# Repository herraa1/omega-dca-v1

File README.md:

# Omega DC Adapter (DCA) v1

DC adapter for the [Omega Home Computer](https://github.com/skiselev/omega).

## Introduction

This is a simple DC adapter for the Omega Home Computer with the following features:

* External DC input power supply
* Wide input voltage from DC +6.5V to DC +24V
* Max input current of 4A
* Power control via external SPDT switch
* Output voltages:
    * 3x independent regulated DC +5V 1.5A (max 3A)
    * 1x independent regulated DC +12V 700mA and -12V 150mA
* Three independent power circuits
* Common Reverse Polarity Protection (RPP), protects the Omega Home Computer from connecting a power barrel with inverted polarity
* Per circuit thermal shutdown, protects the Omega DC Adapter from damage when operating at exceedingly high temperatures
* Per circuit shortcircuit and Over Current Protection (OCP), protects the Omega Home Computer from shorts or excessive current (typ 5.5A)
* Per circuit Over Voltage Protection (OVP), protects the Omega Home Computer from excessive high voltages (typ 5.52V)
* Per circuit Under Voltage Protection (UVP), protects the Omega Home Computer from excessive low voltages (typ ~3V)

## Rationale

When I upgraded my Omega Home Computer with an audio amplifier board and a floppy drive I detected that, no matter how good was the power supply used, the Omega Home Computer suffered sudden resets due to power-related issues when performing some operations like, for example:
* turning on the audio amplifier while the Omega Home Computer was turned on
* increasing the audio amplifier volume up beyond a certain limit when playing compute intensive games
* inserting a floppy disk

My Omega Home Computer was using the [dc-adapter 1.6b](https://msxmakers.design.blog/proyectos/omega-home-computer/mini-fuente-dc-dc/) from [msxmakers!](https://msxmakers.design.blog/) with an external 5V power supply.

I measured the peak power consumption of the Omega Home Computer at about 1.7A with the audio amplifier on and the floppy drive spinning.

I checked several +5V power supplies with no success:
* LJH074-050030W 5V 3A (the one I purchased with the Omega Home Computer kit)
* YU0508 5V 8A (another "white brand" PSU)
* KORAD KA3005P 30V 5A (my lab bench programmable power supply...)

I used an electronic load tester (DL24 150W) and a separate multimeter (VC99) to check the actual voltage of the power supplies under load (at the power supply connector end):
* LJH074-050030W 5V 3A -> dropped to 4.9V with a 2A load and 4.6V with a 3A load
* YU0508 5V 8A -> kept a steady 5.0V with a 3A load, although it went down to 4.7V when pushing it to 6A
* KORAD KA3005P 30V 5A -> dropped to 4.8V at 5V constant voltage with a 2A load, and to 4.7V with a 3A load (required adjusting voltage to 5.3V to get 5.0V at 3A load)

So according to those load tests and the observed peak power consumption, at least the 5V 8A power supply should be capable of powering the Omega Home Computer and its upgrades without issues.
But it was not the case.

So I assumed the specific power demands of the audio amplifier and the floppy drive were causing the problems (undervoltage?) on the power rail of the Omega Home Computer.
I decided to test if the problem went away by using a separate power supply for the audio amplifier/floppy and the Omega Home Computer. I connected two 5V power supplies with a common ground, one power supply to the Omega and the other to the audio amplifier board and floppy. And voilà, no more resets.

So in the end, I decided to design a small power adapter board to provide separate power circuits to the Omega Home Computer, the audio amplifier and video converter, and the floppy drive, and while at it, added several protections just in case something went wrong with the components.

As there are lots of cheap ready to use mini boards providing part of the requirements needed, I just built a "franken-board" cannibalizing other boards to achieve the final goal.
The Omega DC Adapter was born.

## Overview

The Omega DC Adapter is a small power adapter board to provide protected and regulated power to the Omega Home Computer.
It supports the connection of an external DC power supply and a power switch to control power to the computer.

The Omega DC Adapter provides 3 independent power circuits:
* circuit #1 provides power to the Omega Home Computer motherboard and FMPAC (+5V, +12V and -12V) using conectors J10 and J12
* circuit #2 provides power to the external floppy drive (+5V) using connector J8
* circuit #3 provides power to the audio amplifier (+5V) using connector J6 and to the video converter (+5V) using connector J7

## Board

The Omega DC Adapter PCB is a 2-layer design that glues a bunch of ready-to-use mini boards:
* An ideal diode board at U1 to provide Reverse Polarity Protection, i.e. to avoid damage to the Omega Home Computer if a power supply with an incorrect polarity is connected
* Three step down mini boards with thermal shutdown and over current protection at J9, J5 and J3 to provide +5V to the three separate power circuits
* Three over voltage protection mini boards at U2, U3 and U4 to protect the three separate power circuits from overvoltages
* One step up board at J11 to provide +12V and -12V from the 5V output of J9 to feed pins 48 and 50 of the cartridge slots and the FMPAC extension

There are aswell:
* two Positive Temperature Coeficient (PTC) resettable fuses to limit the amount of current delivered to the cartridge slots, as indicated by the [MSX Cartridge Slot](https://www.msx.org/wiki/MSX_Cartridge_slot) specification
* a discharge resistor
* all the necessary connectors

The mini boards are soldered directly to the Omega DC Adapter PCB using pin headers.

### Jumpers

Power circuits #2 and #3 can be merged if desired by populating only J5 and U3 (or J3 and U4) and closing the jumper JP3.
Otherwise, jumper JP3 should always be open.

### Connectors

#### Input Connectors

* J2 2-pin block connector, connects to external DC power supply
* SW1 3-pin block connector, connects to the SPDT power switch in the Omega Home Computer [case](https://github.com/herraa1/omega-case-x3l-v1)

#### Output Connectors

* J10, 8-pin KF2510 power connector (+5V, +12V, -12V, GND), connects to the Omega Home Computer motherboard J10 POWER connector
* J8, 4-pin Berg floppy power connector (+5V, GND), connects to the floppy drive power connector (optional)
* J6, 2-pin XH2.54 audio power connector (+5V, GND), connects to the audio amplifier power connector (optional)
* J7, 2-pin XH2.54 video power connector (+5V, GND), connects to the video converter power connector (optional)
* J12, 3-pin XH2.54 FMPAC power connector (+12V, -12V, GND), connects to the FMPAC board power connector (optional)

## Mini boards

It is recommended to always test all the boards before assembling them to verify that they behave as per their specifications.

### [Ideal Diode Board (U1)](https://www.aliexpress.com/item/1005004921885625.html)

This board provides the reverse polarity protection for the Omega DC Adapter and is based on the 4435 P-MOSFET.

It can work up to 30V 4A and adds minimal voltage drop due to its very low RDS(on) of 20mOhm.
The board works at the external power supply voltage, which must be between +6.5V and +24V as per the Omega DC Adapter design specifications, thus the voltage drop is unimportant in this case.

### [Step Down Boards (J9, J5, J3)](https://www.aliexpress.com/item/1005001608750898.html)

The mini step-down boards are based on the MP2315 high efficient synchronous step down switch mode converter.

This integrated circuit provides thermal shutdown at 150C and has a per-cycle current limit protection, which limits current to a 5.5A typically.
The mini step-down board supports input voltages from 4.5V to 24V, but for the Omega DC Adapter only 6.5V to 24V are supported because of the 5V output required.
Maximum efficiency is around 97% when a 6.5V input voltage is used. When using a 12V input voltage efficiency stays around 94%.
The board can sustain a 2.1A load, with peaks of 3A.

Two different options are available to configure the board for 5V output:
* Option #1: Severing the ADJ trace with a cutter and shorting the 5V pad with a solder blob (you may need a magnifying glass or a soldering microscope to cut the ADJ trace)
* Option #2: Using a screw driver to adjust the trimpot to the desired 5V voltage (or even a little bit more, up to 5.3V)

Option 1 will provide the native 5V voltage of the board, which may be around 5V with an error margin (it could be 4.9V, 5.0V or 5.1V if the board is ok).

Option 2 will configure the board with the selected voltage, which may be difficult to achieve due to the margin of the trimpot. Also, touching the trimpot accidentally can change the output voltage of the board to an undesired voltage (this could be specially dangerous in the 5.4V to 5.5V range, as the over voltage protection won't provide protection there).

It is recommended therefore to use Option #1 with a board that provides 5.0V or 5.1V.

### [Over Voltage Protection Boards (U2, U3, U4)](https://www.aliexpress.com/item/1005001855053619.html)

Over voltage protection is achieved by a dedicated mini board (really mini!) using an unknown IC with SMD marking 905HM.

The board cuts power and turns a red led on when more than 5.5V are detected on the input side of the board. It cuts power too when less than ~3V are detected.
The over voltage protection board supports input voltages up to 30V, so it is on the safe side even if the step down board (which sits before it) causes a short.
The board can sustain a 2.5A load, with peaks of 5A, so it is again within the 2.1A load and 3A peak of the step down board.

### [Step Up Board (J11)](https://www.aliexpress.com/item/1005003879333333.html)

The Step Up board converts the 5V from the step down board at J9 into +12V and -12V, which are then used on the cartridge slot ports and the FMPAC power connector.

The board supports input voltages from 3.3V to 11V, within the margins of the over voltage protection board that provides the input voltage.
On the current side, the board supports a peak 1.8A on the input and provides just a maximum of 700mA for the +12V and 150mA for the -12V.

The cartridge slot ports are protected by 50mA fuses to comply with the max 50mA for all slots MSX specification. 

## Build Instructions

Follow these [Build instructions](Build.md) in order to assemble the Omega DC Adapter board.

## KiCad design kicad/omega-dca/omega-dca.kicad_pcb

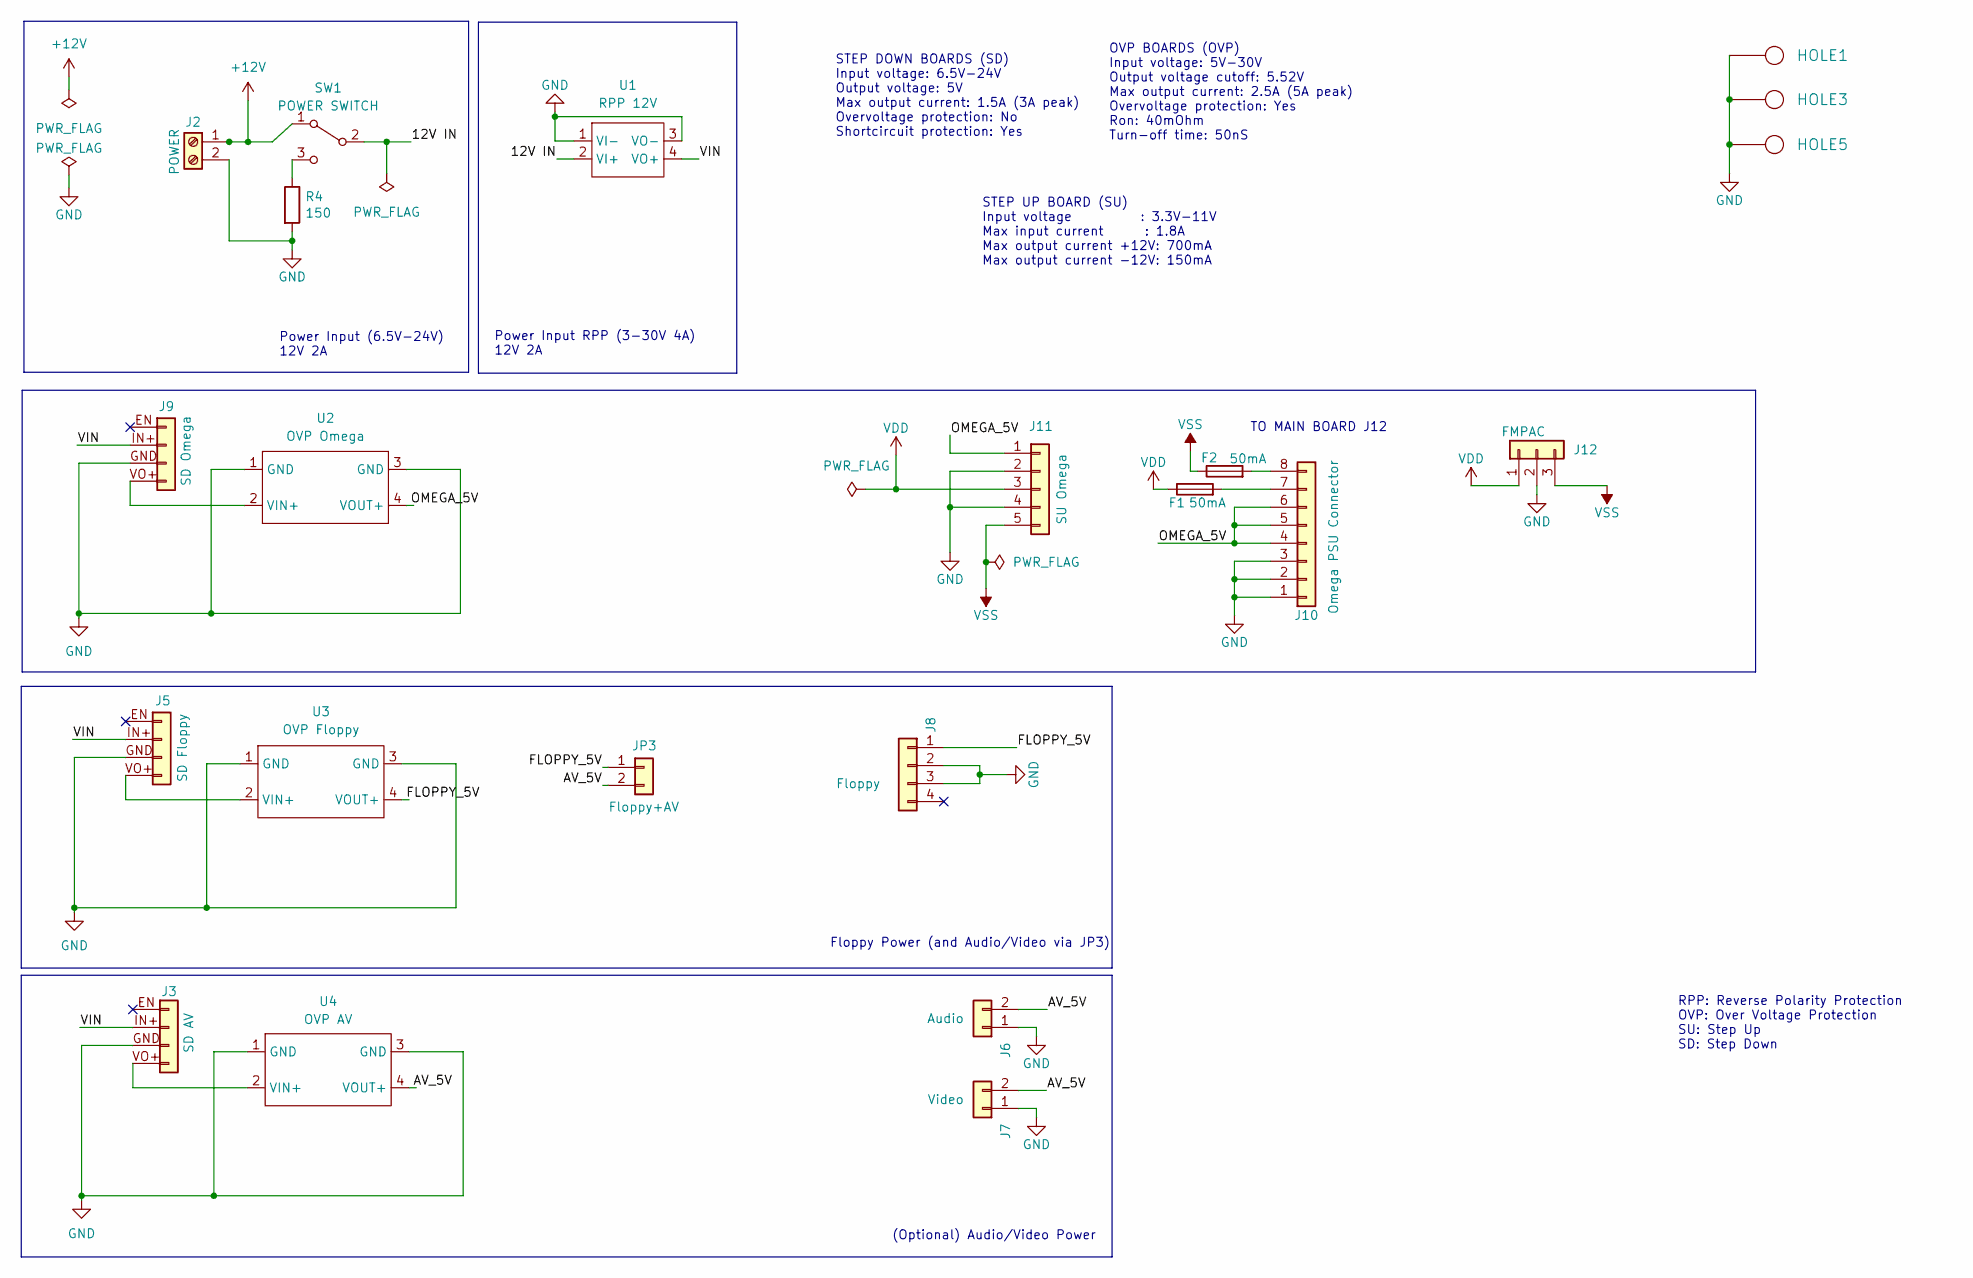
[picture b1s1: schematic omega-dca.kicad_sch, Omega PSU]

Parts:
F1, F2: 50mA; C_Disc_D7.5mm_W2.5mm_P5.00mm
HOLE1, HOLE3, HOLE5: HOLE; Hole_3mm
J2: POWER; Conn_Term_Block_2_5.00mm
J3: SD AV; StepDown_DC-DC_MP2315
J5: SD Floppy; StepDown_DC-DC_MP2315
J6: Audio; JST_XH_B2B-XH-A_1x02_P2.50mm_Vertical
J7: Video; JST_XH_B2B-XH-A_1x02_P2.50mm_Vertical
J8: Floppy; PinHeader_1x04_P2.54mm_Horizontal
J9: SD Omega; StepDown_DC-DC_MP2315
J10: Omega PSU Connector; Conn_Friction_Lock_8P_2.54mm
J11: SU Omega; StepUp_DC-DC_Dual
J12: FMPAC; JST_XH_B3B-XH-A_1x03_P2.50mm_Vertical
JP3: Floppy+AV; Conn_Pin_Header_2x1_2.54mm_NoKey
R4: 150; R_Axial_DIN0207_L6.3mm_D2.5mm_P7.62mm_Horizontal
SW1: POWER SWITCH; Conn_Term_Block_3_5.00mm
U1: RPP 12V; IdealDiode_3-30V-4A
U2: OVP Omega; OVP_Module_5.5V_2.5A_30V
U3: OVP Floppy; OVP_Module_5.5V_2.5A_30V
U4: OVP AV; OVP_Module_5.5V_2.5A_30V

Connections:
+12V: J2.1, SW1.1 (A)
/12V IN: SW1.2 (B), U1.2 (VI+)
/AV_5V: J6.2, J7.2, JP3.2, U4.4 (VOUT+)
/FLOPPY_5V: J8.1, JP3.1, U3.4 (VOUT+)
/OMEGA_5V: J10.4, J10.5, J10.6, J11.1, U2.4 (VOUT+)
/VIN: J3.IN+, J5.IN+, J9.IN+, U1.4 (VO+)
GND: HOLE1.1, HOLE3.1, HOLE5.1, J2.2, J3.GND, J5.GND, J6.1, J7.1, J8.2, J8.3, J9.GND, J10.1, J10.2, J10.3, J11.2, J11.4, J12.2, R4.2, U1.1 (VI-), U1.3 (VO-), U2.1 (GND), U2.3 (GND), U3.1 (GND), U3.3 (GND), U4.1 (GND), U4.3 (GND)
unnamed: F1.2, J10.7
unnamed: F2.2, J10.8
unnamed: J3.VO+, U4.2 (VIN+)
unnamed: J5.VO+, U3.2 (VIN+)
unnamed: J9.VO+, U2.2 (VIN+)
unnamed: R4.1, SW1.3 (C)
VDD: F1.1, J11.3, J12.1
VSS: F2.1, J11.5, J12.3

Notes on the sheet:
Power Input (6.5V-24V) 12V 2A
TO MAIN BOARD J12
STEP UP BOARD (SU) Input voltage : 3.3V-11V Max input current : 1.8A Max output current +12V: 700mA Max output current -12V: 150mA
RPP: Reverse Polarity Protection OVP: Over Voltage Protection SU: Step Up SD: Step Down
Power Input RPP (3-30V 4A) 12V 2A
(Optional) Audio/Video Power
STEP DOWN BOARDS (SD) Input voltage: 6.5V-24V Output voltage: 5V Max output current: 1.5A (3A peak) Overvoltage protection: No Shortcircuit protection: Yes
OVP BOARDS (OVP) Input voltage: 5V-30V Output voltage cutoff: 5.52V Max output current: 2.5A (5A peak) Overvoltage protection: Yes Ron: 40mOhm Turn-off time: 50nS
Floppy Power (and Audio/Video via JP3)

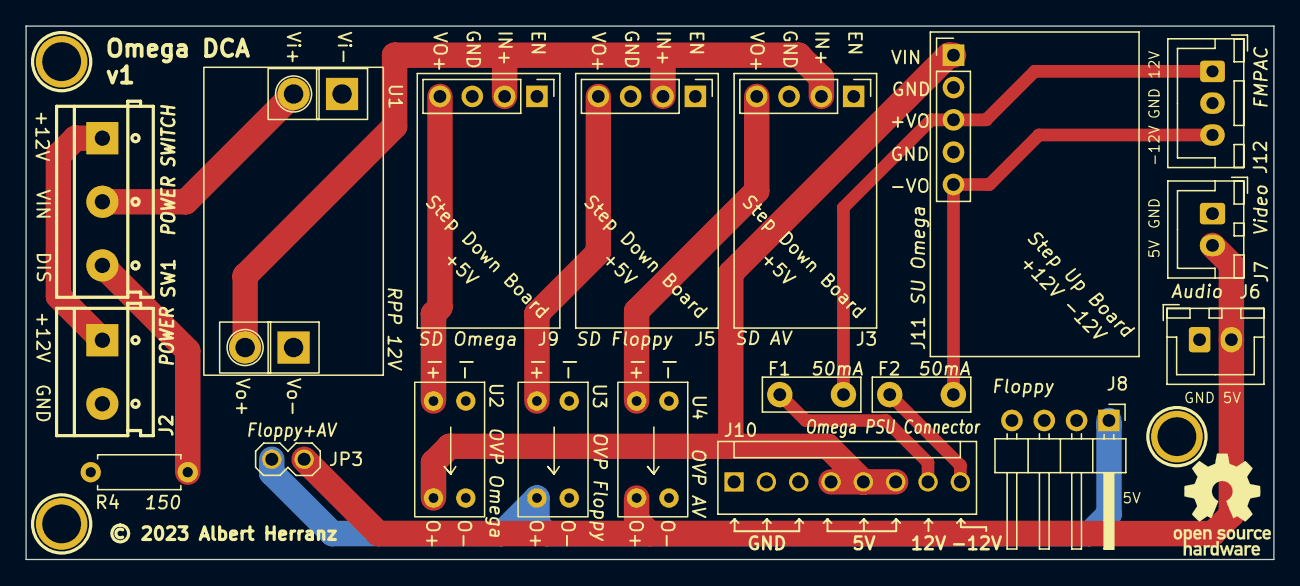
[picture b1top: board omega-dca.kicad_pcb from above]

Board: 2 copper layers, 98.0 x 41.9 mm, 22 parts (0 on the bottom side), 15 nets.

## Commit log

2023-07-15 Initial commit.
2023-07-15 small redaction fixes
2023-07-23 Small redaction fixes, and preparation for build instructions
2023-07-23 Add build instructions

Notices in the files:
kicad/omega-dca/omega-dca.kicad_pcb:
© 2023 Albert Herranz
